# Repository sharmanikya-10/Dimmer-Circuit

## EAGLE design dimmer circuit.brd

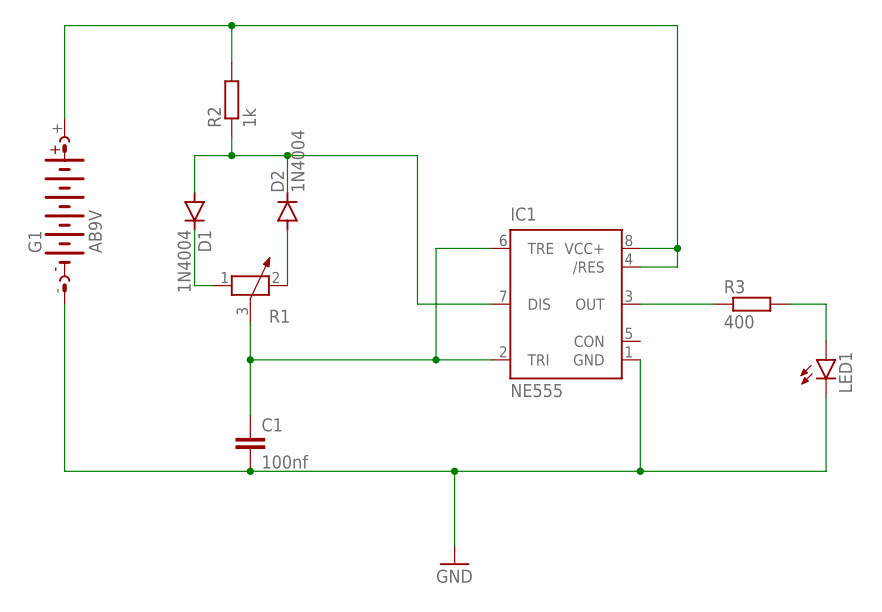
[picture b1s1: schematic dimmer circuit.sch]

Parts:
C1: 100nf; C025-025X050
D1, D2: 1N4004; DO41-10
G1: AB9V
IC1: NE555; DIL-08
LED1: LED5MM
R1: POTENTIOMETER_PT-10; PT-10
R2: 1k; 0204/7
R3: 400; 0204/7

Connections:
GND: C1.2, G1.-, IC1.1 (GND), LED1.K (C)
unnamed: D2.A, R1.2
unnamed: D1.C, R1.1
unnamed: C1.1, IC1.2 (TRI), IC1.6 (TRE), R1.3
unnamed: D1.A, D2.C, IC1.7 (DIS), R2.1
unnamed: G1.+, IC1.4 (/RES), IC1.8 (VCC+), R2.2
unnamed: IC1.3 (OUT), R3.1
unnamed: LED1.A, R3.2

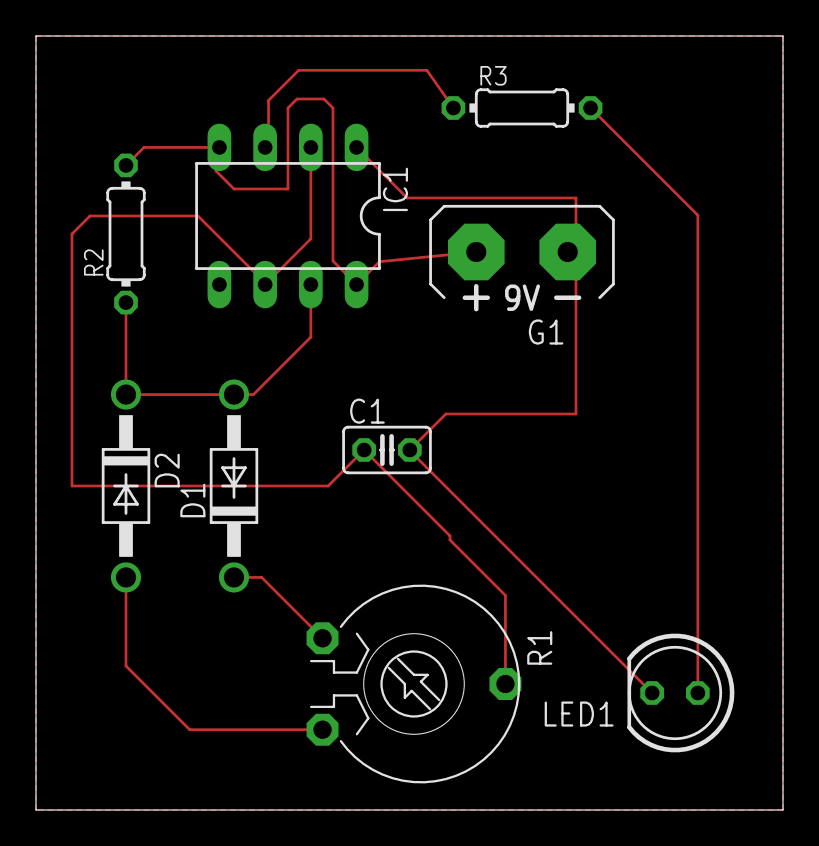
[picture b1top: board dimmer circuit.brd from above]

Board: 2 copper layers, 41.5 x 43.0 mm, 9 parts (0 on the bottom side), 8 nets.

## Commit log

2022-09-08 Added Files
